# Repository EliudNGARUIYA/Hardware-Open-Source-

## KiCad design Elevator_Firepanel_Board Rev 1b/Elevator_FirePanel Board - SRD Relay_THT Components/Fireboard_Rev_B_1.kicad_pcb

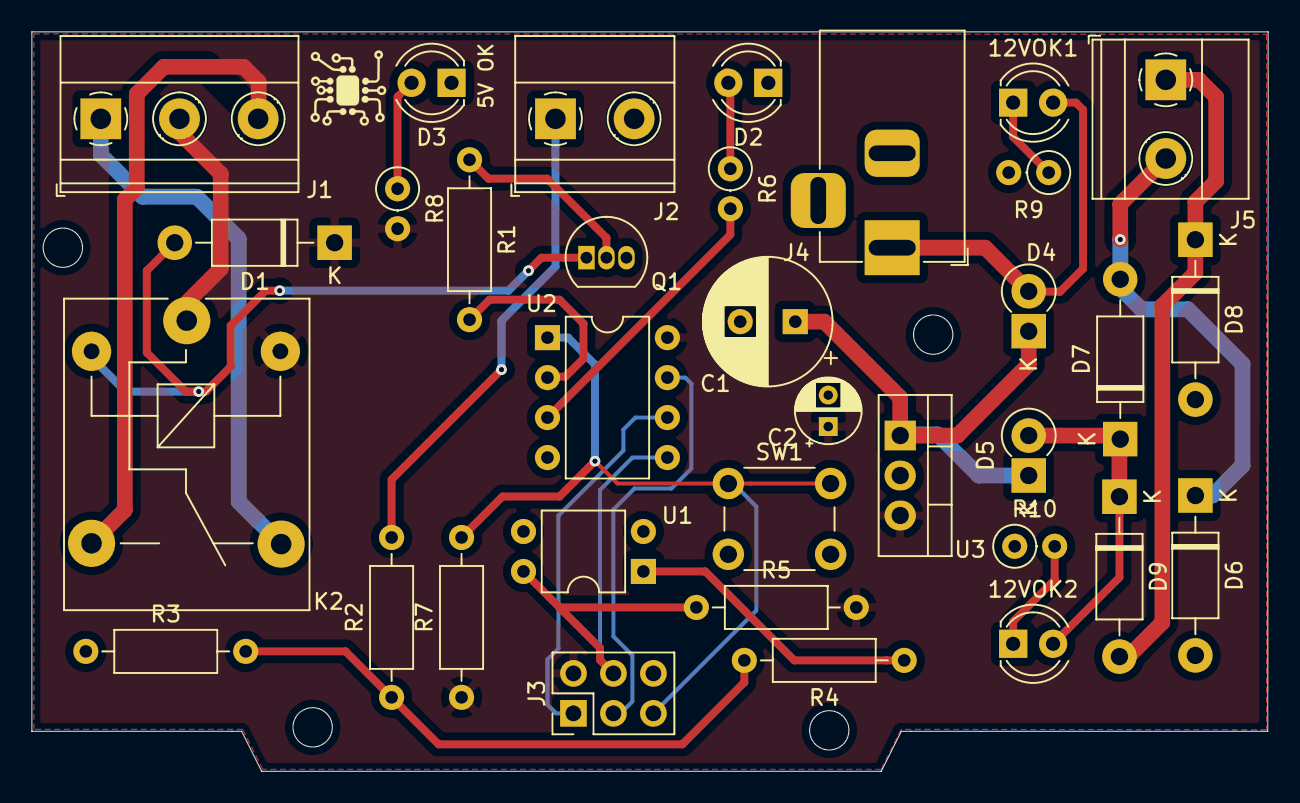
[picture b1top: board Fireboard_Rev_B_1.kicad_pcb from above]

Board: 2 copper layers, 78.6 x 47.0 mm, 34 parts (0 on the bottom side), 25 nets.

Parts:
12VOK1: Yellow; LED_D4.0mm
12VOK2: Blue; LED_D4.0mm
C1: 100uF 35V; CP_Radial_D8.0mm_P3.50mm
C2: 10uF 35V; CP_Radial_D4.0mm_P2.00mm
D1: 1N4001; D_DO-41_SOD81_P10.16mm_Horizontal
D2: Red; LED_D4.0mm
D3: Green; LED_D4.0mm
D4, D5: D; D_DO-41_SOD81_P2.54mm_Vertical_KathodeUp
D6, D7, D8, D9: 1N4007; D_DO-41_SOD81_P10.16mm_Horizontal
J1: Output; TerminalBlock_Phoenix_MKDS-1,5-3_1x03_P5.00mm_Horizontal
J2: Input; TerminalBlock_Phoenix_MKDS-1,5-2_1x02_P5.00mm_Horizontal
J3: ICSP; PinHeader_2x03_P2.54mm_Vertical
J4: DC_IN; BarrelJack_Horizontal
J5: AC_IN; TerminalBlock_Phoenix_MKDS-1,5-2_1x02_P5.00mm_Horizontal
K2: SANYOU_SRD_Form_C; Relay_SPDT_SANYOU_SRD_Series_Form_C
Q1: BC547; TO-92_Inline
R1, R4, R7: 10K; R_Axial_DIN0207_L6.3mm_D2.5mm_P10.16mm_Horizontal
R2: 2K; R_Axial_DIN0207_L6.3mm_D2.5mm_P10.16mm_Horizontal
R3: 1K; R_Axial_DIN0207_L6.3mm_D2.5mm_P10.16mm_Horizontal
R5: 4.7K; R_Axial_DIN0207_L6.3mm_D2.5mm_P10.16mm_Horizontal
R6, R8, R9, R10: 330; R_Axial_DIN0207_L6.3mm_D2.5mm_P2.54mm_Vertical
SW1: SW_Push; SW_PUSH_6mm_H4.3mm
U1: PC817; DIP-4_W7.62mm
U2: ATtiny13-20PU; DIP-8_W7.62mm
U3: LM7805_TO220; TO-220-3_Vertical

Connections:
+5V: C2.1, D1.1, J3.2, K2.5, R5.2, R7.1, R8.2, U2.8, U3.3
+12V: C1.1, D4.1, D5.1, U3.1
/ACL: D6.1, D7.2, J5.2
/ACN: D8.1, D9.2, J5.1
/DC+: 12VOK2.2, D5.2, D7.1, D9.1
/Rela_y: R6.2, U2.3
/Relay: R1.2, U2.2
GND: C1.2, C2.2, D2.1, D3.1, D6.2, D8.2, J2.2, J3.6, J4.2, Q1.3, R3.1, R9.2, R10.1, SW1.2, U1.2, U1.3, U2.4, U3.2
MISO: J3.1, U2.6
MOSI: J3.4, R5.1, U1.4, U2.5
unnamed: 12VOK1.1, R9.1
unnamed: 12VOK1.2, D4.2, J4.1
unnamed: 12VOK2.1, R10.2
unnamed: D1.2, K2.2, Q1.1
unnamed: D2.2, R6.1
unnamed: D3.2, R8.1
unnamed: J1.1, K2.4
unnamed: J1.2, K2.1
unnamed: J1.3, K2.3
unnamed: J2.1, R2.2
unnamed: Q1.2, R1.1
unnamed: R2.1, R3.2, R4.2
unnamed: R4.1, U1.1
PB2: J3.3, U2.7
Reset: J3.5, R7.2, SW1.1, U2.1

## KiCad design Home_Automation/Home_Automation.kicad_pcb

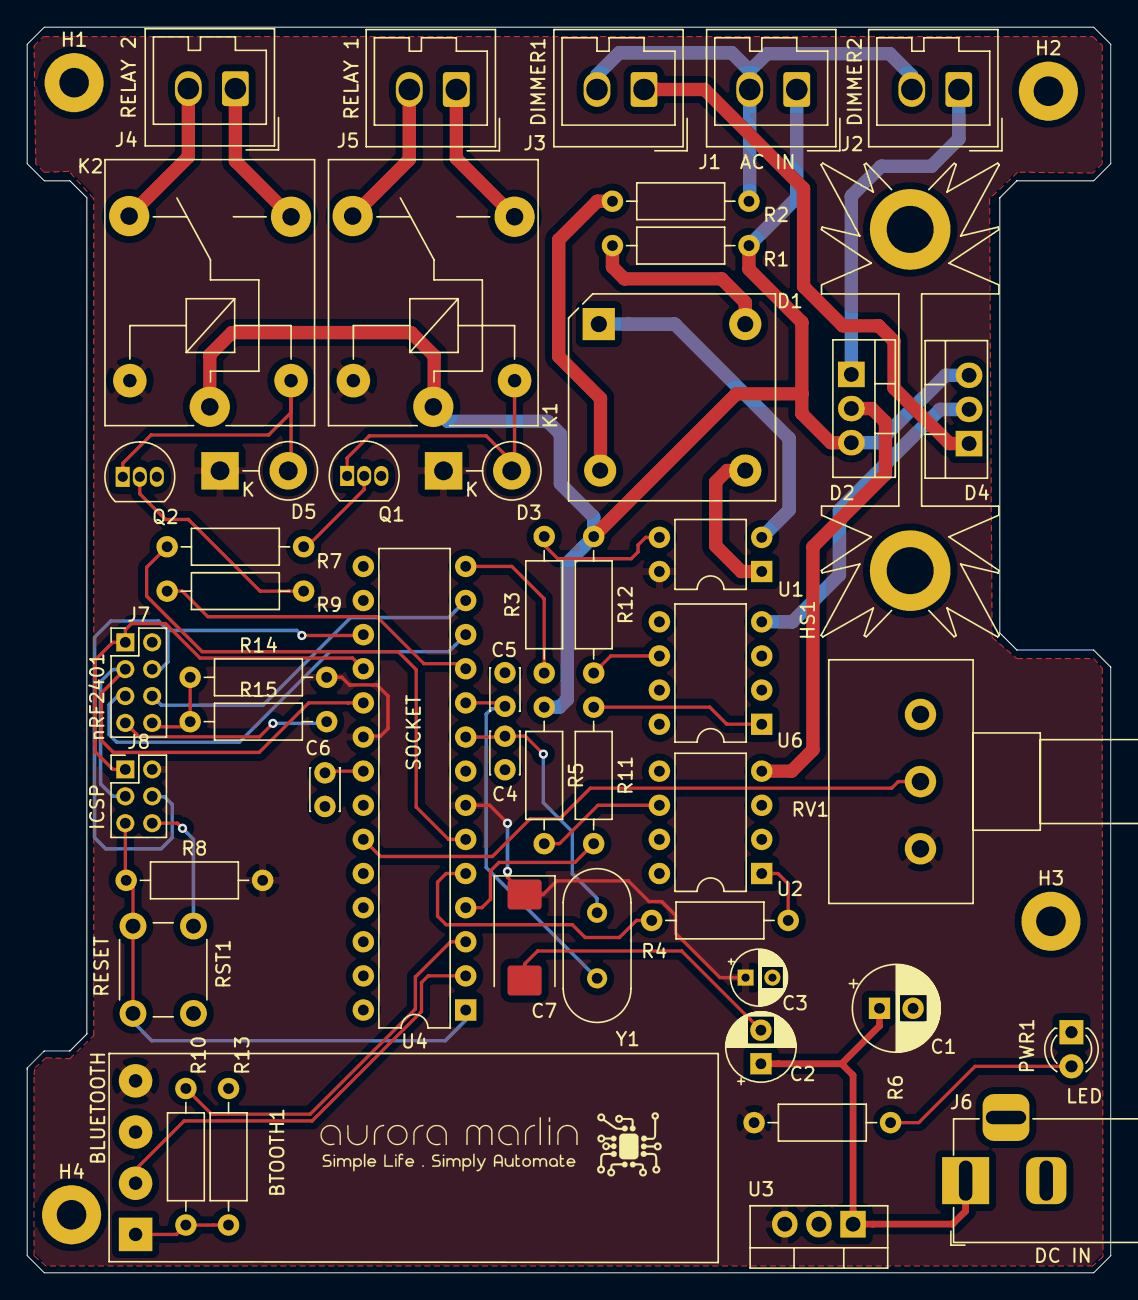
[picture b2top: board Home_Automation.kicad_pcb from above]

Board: 2 copper layers, 80.6 x 92.7 mm, 55 parts (0 on the bottom side), 46 nets.

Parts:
BTOOTH1: BTooth; SolderWirePad_1x04_P3.81mm_Drill1mm
C1: 470uF 50v; CP_Radial_D6.3mm_P2.50mm
C2: 100uF 50V; CP_Radial_D5.0mm_P2.50mm
C3: 10uF 50V; CP_Radial_D4.0mm_P2.00mm
C4, C5: 22pF; C_Disc_D3.0mm_W2.0mm_P2.50mm
C6: 100nF; C_Disc_D3.0mm_W2.0mm_P2.50mm
C7: 100nF; CP_EIA-7343-30_AVX-N_Pad2.25x2.55mm_HandSolder
D1: D_Bridge_-A+A; Diode_Bridge_15.2x15.2x6.3mm_P10.9mm
D2, D4: Q_TRIAC_A1GA2; TO-220-3_Vertical
D3, D5: 1N4001; D_5W_P5.08mm_Vertical_KathodeUp
H1, H2, H3, H4: M2; MountingHole_2.2mm_M2_Pad
HS1: Heatsink; Heatsink_Fischer_SK104-STCB_35x13mm__2xDrill3.5mm_ScrewM3
J1: AC_IN; Wago_734-132_1x02_P3.50mm_Vertical
J2: AC_OUT_1; Wago_734-132_1x02_P3.50mm_Vertical
J3: AC_OUT_2; Wago_734-132_1x02_P3.50mm_Vertical
J4: Relay_1; Wago_734-132_1x02_P3.50mm_Vertical
J5: Relay_2; Wago_734-132_1x02_P3.50mm_Vertical
J6: DC_IN; BarrelJack_Horizontal
J7: nRF24L01; PinHeader_2x04_P2.00mm_Vertical
J8: ICSP; PinHeader_2x03_P2.00mm_Vertical
K1, K2: SANYOU_SRD_Form_C; Relay_SPDT_SANYOU_SRD_Series_Form_C
LOGO1: Logo; aurora_Marlin
PWR1: Green; LED_D3.0mm
Q1, Q2: BC549; TO-92_Inline
R1, R2: 47K; R_Axial_DIN0207_L6.3mm_D2.5mm_P10.16mm_Horizontal
R3, R13, R14: 1K; R_Axial_DIN0207_L6.3mm_D2.5mm_P10.16mm_Horizontal
R4, R11: 100R; R_Axial_DIN0207_L6.3mm_D2.5mm_P10.16mm_Horizontal
R5, R12: 200R; R_Axial_DIN0207_L6.3mm_D2.5mm_P10.16mm_Horizontal
R6: 330R; R_Axial_DIN0207_L6.3mm_D2.5mm_P10.16mm_Horizontal
R7, R8, R9: 10K; R_Axial_DIN0207_L6.3mm_D2.5mm_P10.16mm_Horizontal
R10, R15: 2K; R_Axial_DIN0207_L6.3mm_D2.5mm_P10.16mm_Horizontal
RST1: RESET; SW_PUSH_6mm_H7.3mm
RV1: R_POT; Potentiometer_Alps_RK163_Single_Horizontal
U1: EL817; DIP-4_W7.62mm
U2, U6: MOC3020M; DIP-8_W7.62mm
U3: L7805; TO-220-3_Vertical
U4: ATmega168P-20PU; DIP-28_W7.62mm
Y1: 16MHz; Crystal_HC49-4H_Vertical

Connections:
+5V: BTOOTH1.4, C3.1, C7.1, D3.1, D5.1, J8.2, K1.5, K2.5, R6.1, R8.2, R14.2, RV1.1, U1.4, U3.3, U4.7, U4.20
+12V: C1.1, C2.1, J6.1, U3.1
/AC_L: D2.3, D4.3, J1.1, K1.1, K2.1, R1.2, R5.1, R12.1
/AC_LOUT: D2.1, J2.1
/AC_LOUT_1: D4.1, J3.1
/AC_N: J1.2, J2.2, J3.2, R2.2
/Controller Circuit/POT: RV1.2, U4.23
/Controller Circuit/Rx: R13.1, U4.3
/Controller Circuit/Tx: BTOOTH1.2, U4.2
/Diac_Control: R4.2, U4.5
/Diac_Control_1: R11.2, U4.4
/NC: J5.2, K1.4
/NC_1: J4.2, K2.4
/NO: J5.1, K1.3
/NO_1: J4.1, K2.3
/Rel_1: R7.1, U4.6
/Rel_2: R9.1, U4.11
/ZCD+: D1.3, U1.1
/ZCD-: D1.1, U1.2
/Z_Cross_Detect: R3.1, U4.14
CE: J7.5, U4.12
CS: J7.6, U4.13
GND: BTOOTH1.3, C1.2, C2.2, C3.2, C4.2, C5.2, C6.2, C7.2, H1.1, H2.1, H3.1, H4.1, J6.2, J7.7, J8.6, PWR1.1, Q1.3, Q2.3, R10.2, R15.2, RST1.2, RV1.3, U2.2, U3.2, U4.8, U4.22, U6.2
MISO: J7.1, J8.1, U4.18
MOSI: J7.4, J8.4, U4.17
unnamed: BTOOTH1.1, R10.1, R13.2
unnamed: C6.1, U4.21
unnamed: D1.2, R2.1
unnamed: D1.4, R1.1
unnamed: D2.2, U2.4
unnamed: D3.2, K1.2, Q1.1
unnamed: D4.2, U6.4
unnamed: D5.2, K2.2, Q2.1
unnamed: J7.8, R14.1, R15.1
unnamed: PWR1.2, R6.2
unnamed: Q1.2, R7.2
unnamed: Q2.2, R9.2
unnamed: R3.2, U1.3
unnamed: R4.1, U2.1
unnamed: R5.2, U2.6
unnamed: R11.1, U6.1
unnamed: R12.2, U6.6
PB5: J7.3, J8.3, U4.19
Reset: J8.5, R8.1, RST1.1, U4.1
XTAL1: C4.1, U4.9, Y1.1
XTAL2: C5.1, U4.10, Y1.2

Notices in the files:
Elevator_Firepanel_Board Rev 1b/Elevator_FirePanel Board - SRD Relay_THT Components/Fireboard_Rev_B_1.kicad_pcb:
© Aurora Marlin LLC
